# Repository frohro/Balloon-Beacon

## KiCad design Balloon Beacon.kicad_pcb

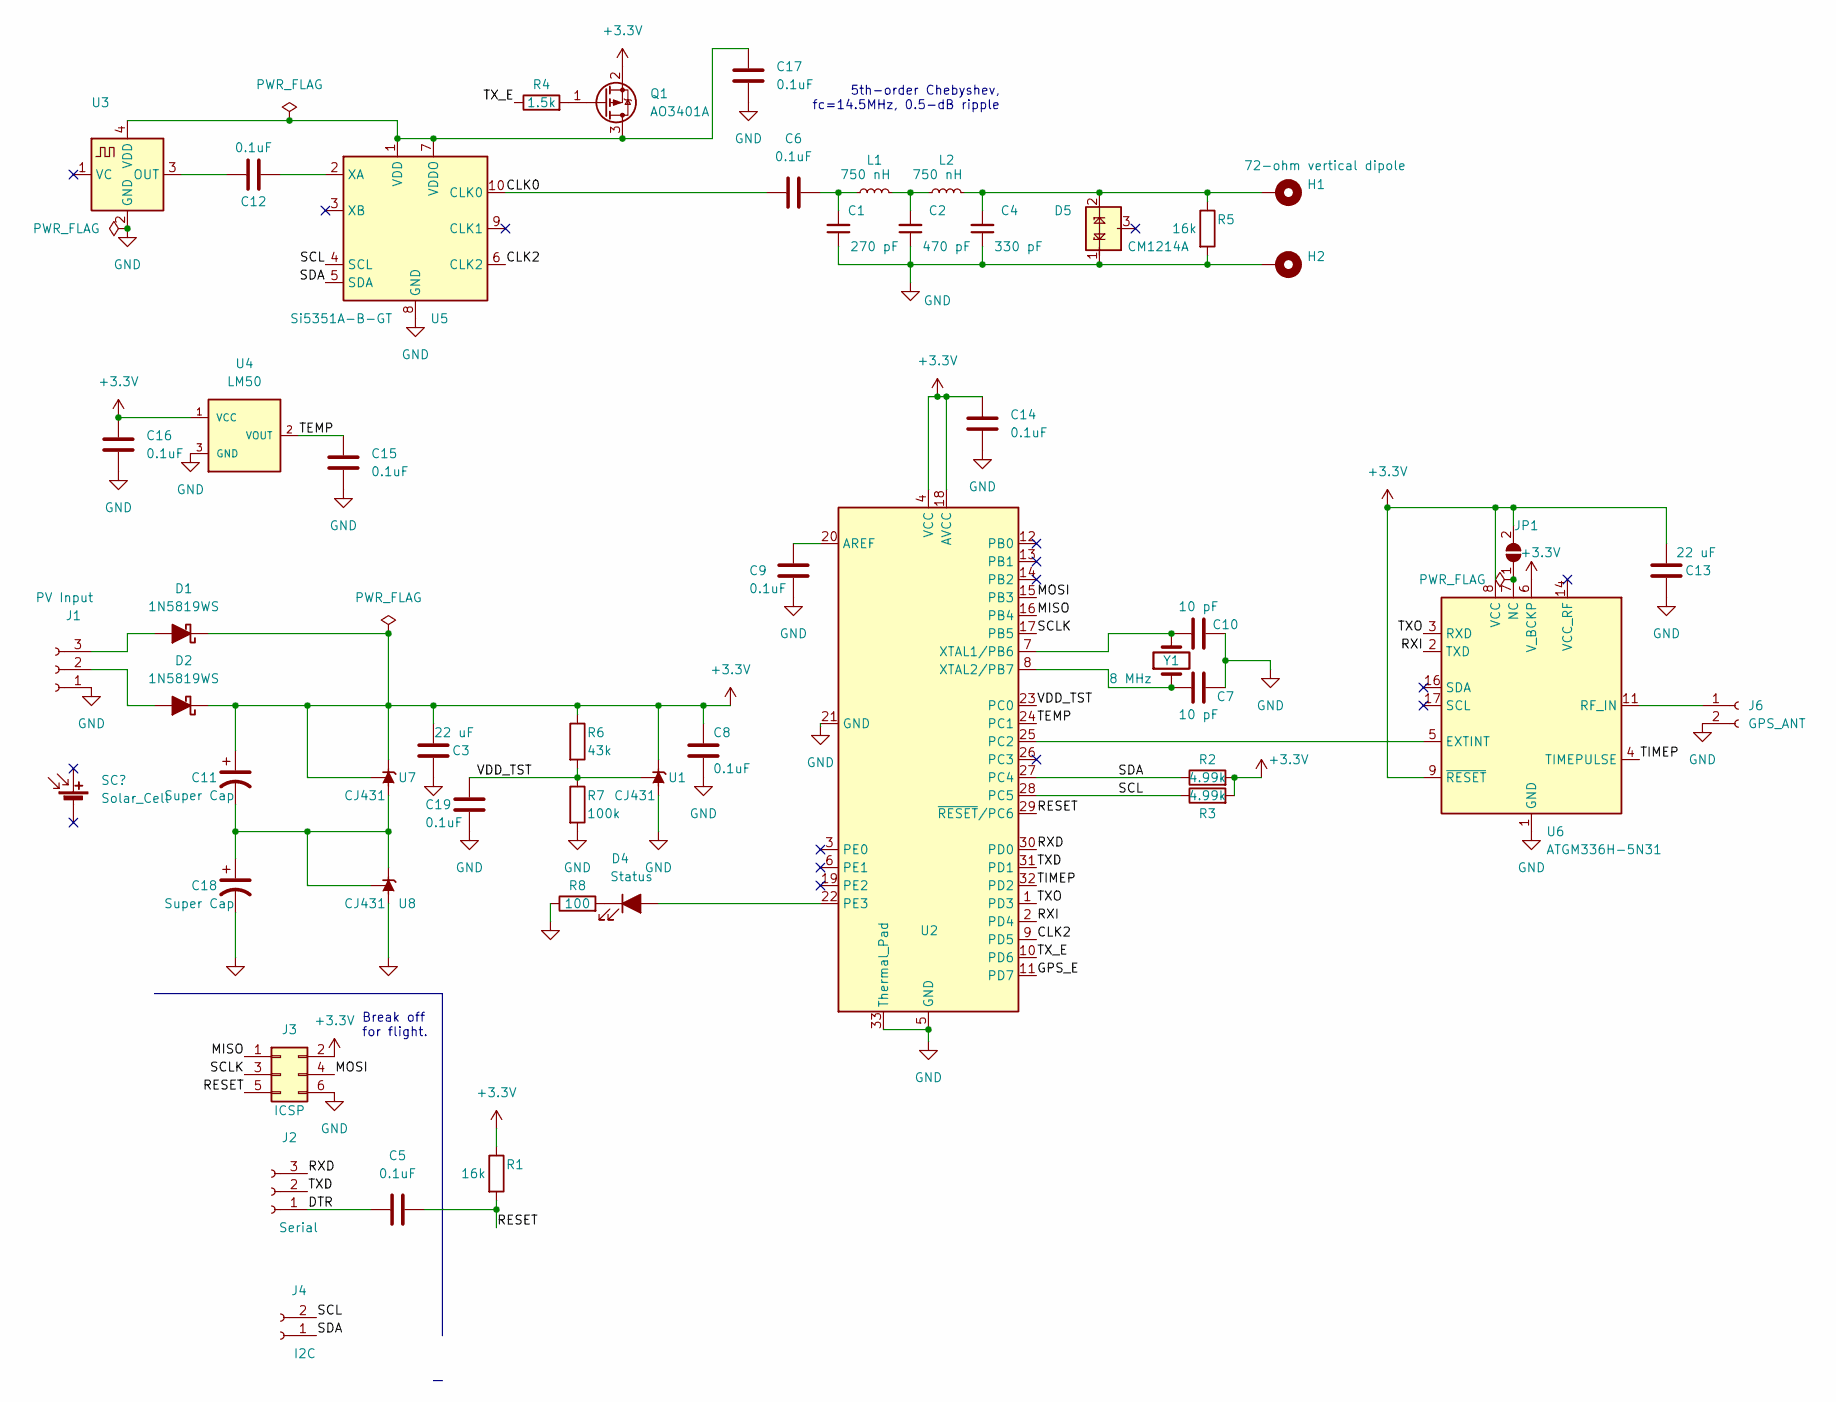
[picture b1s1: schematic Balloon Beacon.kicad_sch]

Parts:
C1: 270 pF; C_0805_2012Metric
C2: 470 pF; C_0603_1608Metric; LCSC C1620
C3, C13: 22 uF; C_0603_1608Metric; LCSC C59461
C4: 330 pF; C_0805_2012Metric; LCSC C51207
C5, C6, C8, C9, C12, C14, C15, C16, C17, C19: 0.1uF; C_0402_1005Metric; LCSC C1525
C7, C10: 10 pF; C_0603_1608Metric; LCSC C1634
C11, C18: Super Cap; CP_Radial_D18.0mm_P7.50mm
D1, D2: 1N5819WS; D_SOD-323; LCSC C191023
D4: Status; LED_0805_2012Metric; LCSC C2293
D5: CM1214A; SOT-23
H1, H2: 72-ohm vertical dipole; PinHeader_1x01_P2.54mm_Vertical
J1: PV Input; PinHeader_1x03_P2.54mm_Vertical
J2: Serial; PinHeader_1x03_P2.54mm_Vertical
J3: ICSP; PinHeader_2x03_P2.54mm_Vertical
J4: I2C; PinHeader_1x02_P2.54mm_Vertical
J6: GPS_ANT; PinHeader_1x02_P2.54mm_Vertical
JP1: SolderJumper_2_Open; SolderJumper-2_P1.3mm_Open_TrianglePad1.0x1.5mm
L1, L2: 750 nH; L_1008_2520Metric
Q1: AO3401A; SOT-23; LCSC C15127
R1, R5: 16k; R_0603_1608Metric; LCSC C17490
R2, R3: 4.99k; R_0603_1608Metric; LCSC C23046
R4: 1.5k; R_0603_1608Metric_Pad0.98x0.95mm_HandSolder; LCSC C22843
R6: 43k; R_0603_1608Metric; LCSC C23172
R7: 100k; R_0402_1005Metric; LCSC C25741
R8: 100; R_0603_1608Metric_Pad0.98x0.95mm_HandSolder; LCSC C22775
U1, U7, U8: CJ431; SOT-23; LCSC C3113
U2, U3: (no value)
U4: LM50; SOT-23; LCSC C411880
U5: Si5351A-B-GT; MSOP-10_3x3mm_P0.5mm; LCSC C504891
U6: ATGM336H-5N31; ublox_MAX; LCSC C90770
Y1: 8 MHz; Crystal_SMD_5032-2Pin_5.0x3.2mm; Digikey 5032S20800BMDAEDENA-CT

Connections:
+3V3: C3.1, C8.1, C11.1, C13.1, C14.1, C16.1, D1.1 (K), D2.1 (K), J3.2, JP1.2 (B), Q1.2 (S), R1.1, R2.2, R3.2, R6.1, U1.1 (K), U2.4 (VCC), U2.18 (AVCC), U4.1 (VCC), U6.6 (V_BCKP), U6.8 (VCC), U6.9 (~RESET), U7.1 (K), U7.2 (REF)
/CLK0: C6.1, U5.10 (CLK0)
/CLK2: U2.9 (PD5), U5.6 (CLK2)
/DTR: C5.1, J2.1
/GPS_E: U2.11 (PD7)
/MISO: J3.1, U2.16 (PB4)
/MOSI: J3.4, U2.15 (PB3)
/RESET: C5.2, J3.5, R1.2, U2.29 (~RESET/PC6)
/RXD: J2.3, U2.30 (PD0)
/RXI: U2.2 (PD4), U6.2 (TXD)
/SCL: J4.2, R3.1, U2.28 (PC5), U5.4 (SCL)
/SCLK: J3.3, U2.17 (PB5)
/SDA: J4.1, R2.1, U2.27 (PC4), U5.5 (SDA)
/TEMP: C15.1, U2.24 (PC1), U4.2 (VOUT)
/TIMEP: U2.32 (PD2), U6.4 (TIMEPULSE)
/TXD: J2.2, U2.31 (PD1)
/TXO: U2.1 (PD3), U6.3 (RXD)
/TX_E: R4.1, U2.10 (PD6)
/VDD_TST: C19.1, R6.2, R7.1, U1.2 (REF), U2.23 (PC0)
GND: C1.1, C2.1, C3.2, C4.1, C7.2, C8.2, C9.2, C10.2, C13.2, C14.2, C15.2, C16.2, C17.2, C18.2, C19.2, D5.1 (VP), H2.1, J1.1, J3.6, J6.2, R5.2, R7.2, R8.1, U1.3 (A), U2.5 (GND), U2.21 (GND), U2.33 (Thermal_Pad), U3.2 (GND), U4.3 (GND), U5.8 (GND), U6.1 (GND), U6.10 (GND), U6.12 (GND), U8.3 (A)
unnamed: C1.2, C6.2, L1.1
unnamed: C2.2, L1.2, L2.1
unnamed: C4.2, D5.2 (VN), H1.1, L2.2, R5.1
unnamed: C7.1, U2.8 (XTAL2/PB7), Y1.1
unnamed: C9.1, U2.20 (AREF)
unnamed: C10.1, U2.7 (XTAL1/PB6), Y1.2
unnamed: C11.2, C18.1, U7.3 (A), U8.1 (K), U8.2 (REF)
unnamed: C12.1, U5.2 (XA)
unnamed: C12.2, U3.3 (OUT)
unnamed: C17.1, Q1.3 (D), U3.4 (VDD), U5.1 (VDD), U5.7 (VDDO)
unnamed: D1.2 (A), J1.3
unnamed: D2.2 (A), J1.2
unnamed: D4.1 (K), R8.2
unnamed: D4.2 (A), U2.22 (PE3)
unnamed: J6.1, U6.11 (RF_IN)
unnamed: JP1.1 (A), U6.7 (NC)
unnamed: Q1.1 (G), R4.2
unnamed: U2.25 (PC2), U6.5 (EXTINT)

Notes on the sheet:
Break off for flight.
5th-order Chebyshev, fc=14.5MHz, 0.5-dB ripple

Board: 2 copper layers, 51 parts (0 on the bottom side), 37 nets, no tracks yet.

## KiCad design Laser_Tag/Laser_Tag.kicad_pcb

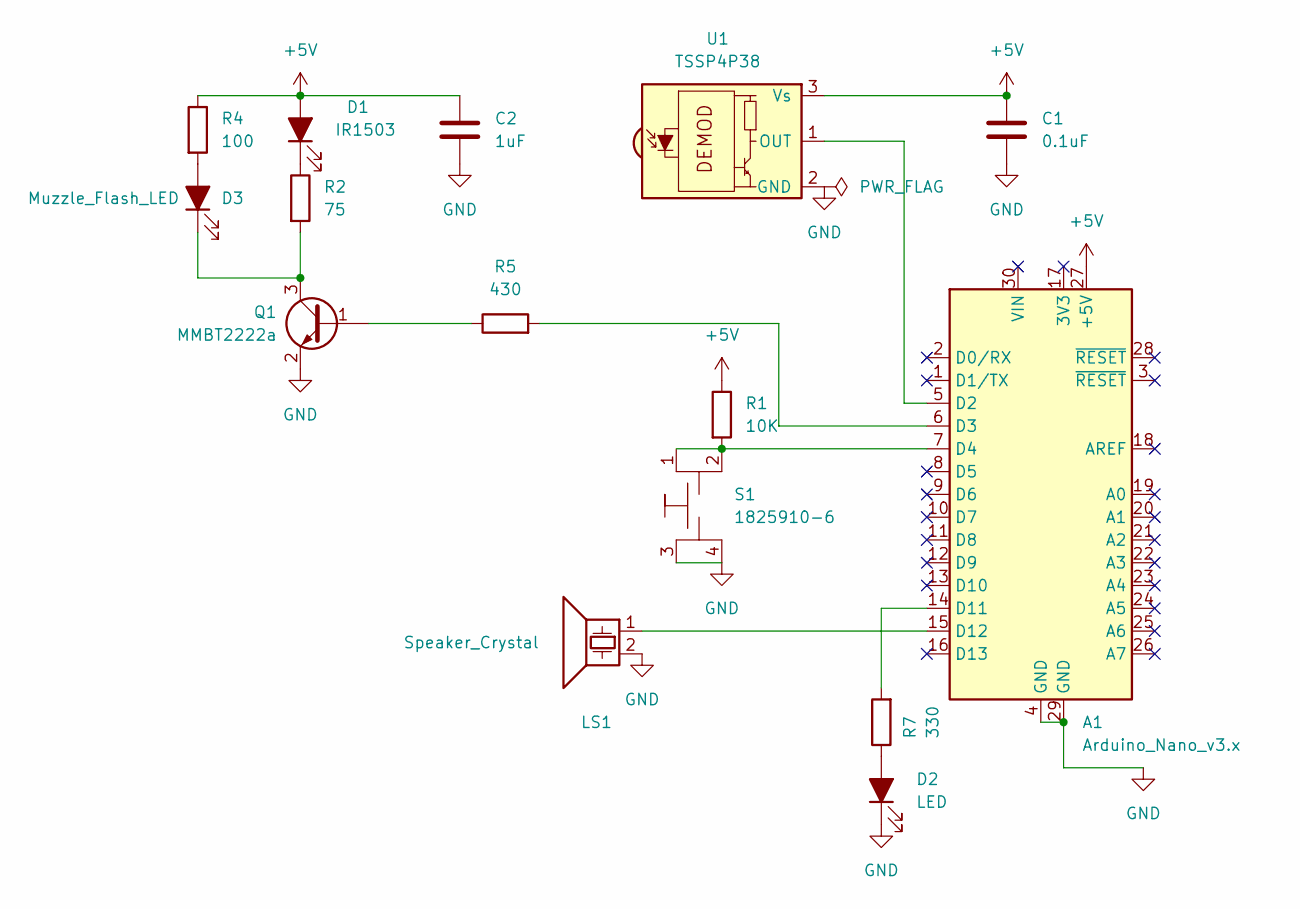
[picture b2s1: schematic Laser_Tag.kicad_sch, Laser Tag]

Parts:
A1: Arduino_Nano_v3.x; Arduino_Nano
C1: 0.1uF; C_0805_2012Metric
C2: 1uF; C_0805_2012Metric
D1: IR1503; LED_D5.0mm
D2: LED; LED_D5.0mm
D3: Muzzle_Flash_LED; LED_D5.0mm
LS1: Speaker_Crystal; Buzzer_12x9.5RM7.6
Q1: MMBT2222a; SOT-23
R1: 10K; R_0805_2012Metric
R2: 75; R_0805_2012Metric
R4: 100; R_0805_2012Metric
R5: 430; R_0805_2012Metric
R7: 330; R_0805_2012Metric
S1: 1825910-6; SW_PUSH_6mm_H4.3mm_4_pin
U1: TSSP4P38; Vishay_MINICAST-3Pin

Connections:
+5V: A1.27 (+5V), C1.1, C2.1, D1.2 (A), R1.1, R4.1, U1.3 (Vs)
GND: A1.4 (GND), A1.29 (GND), C1.2, C2.2, D2.1 (K), LS1.2, Q1.2 (E), S1.3, S1.4 (3), U1.2 (GND)
unnamed: A1.5 (D2), U1.1 (OUT)
unnamed: A1.6 (D3), R5.2
unnamed: A1.7 (D4), R1.2, S1.1, S1.2
unnamed: A1.14 (D11), R7.2
unnamed: A1.15 (D12), LS1.1
unnamed: D1.1 (K), R2.1
unnamed: D2.2 (A), R7.1
unnamed: D3.1 (K), Q1.3 (C), R2.2
unnamed: D3.2 (A), R4.2
unnamed: Q1.1 (B), R5.1

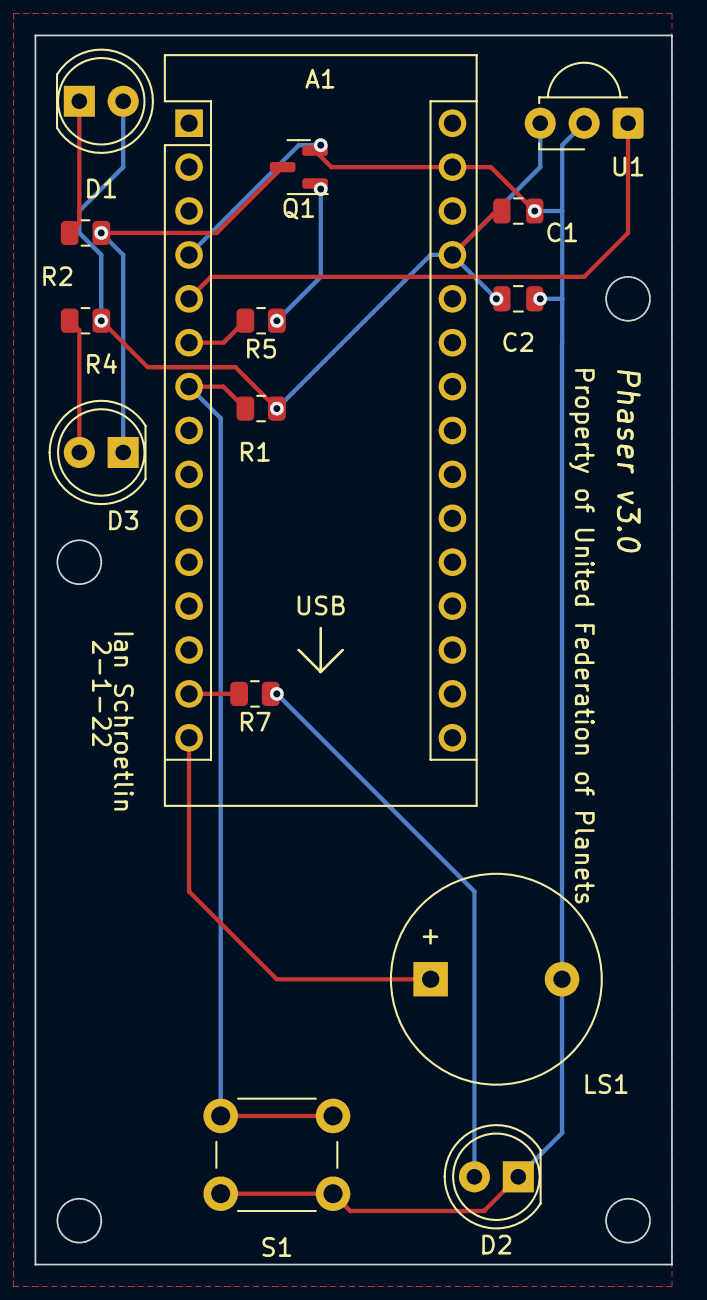
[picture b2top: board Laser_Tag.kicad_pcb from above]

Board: 2 copper layers, 36.8 x 71.1 mm, 15 parts (0 on the bottom side), 12 nets.

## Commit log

2022-02-14 removed oops!
2022-02-14 Last minute schematic changes....
2022-02-14 Rules check fixes...
2022-02-14 Added .gitignore
2022-02-14 Deleted note on schematic and added footprint for jumper.
2022-02-14 Fixed no connect on GPS...
2022-02-15 Added a solar cell so you can see what might work...
2022-02-24 Changed JLCPCB to LCSC for compatibility with https://support.jlcpcb.com/article/84-how-to-generate-the-bom-and-centroid-file-from-kicad
2022-02-25 added BOM for JLCPCB.
2022-04-27 Changed TCXO to an available one.
2022-04-27 Add ZachTech Firmware submodule
2022-04-28 Deleted a solar cell on the schematic.
